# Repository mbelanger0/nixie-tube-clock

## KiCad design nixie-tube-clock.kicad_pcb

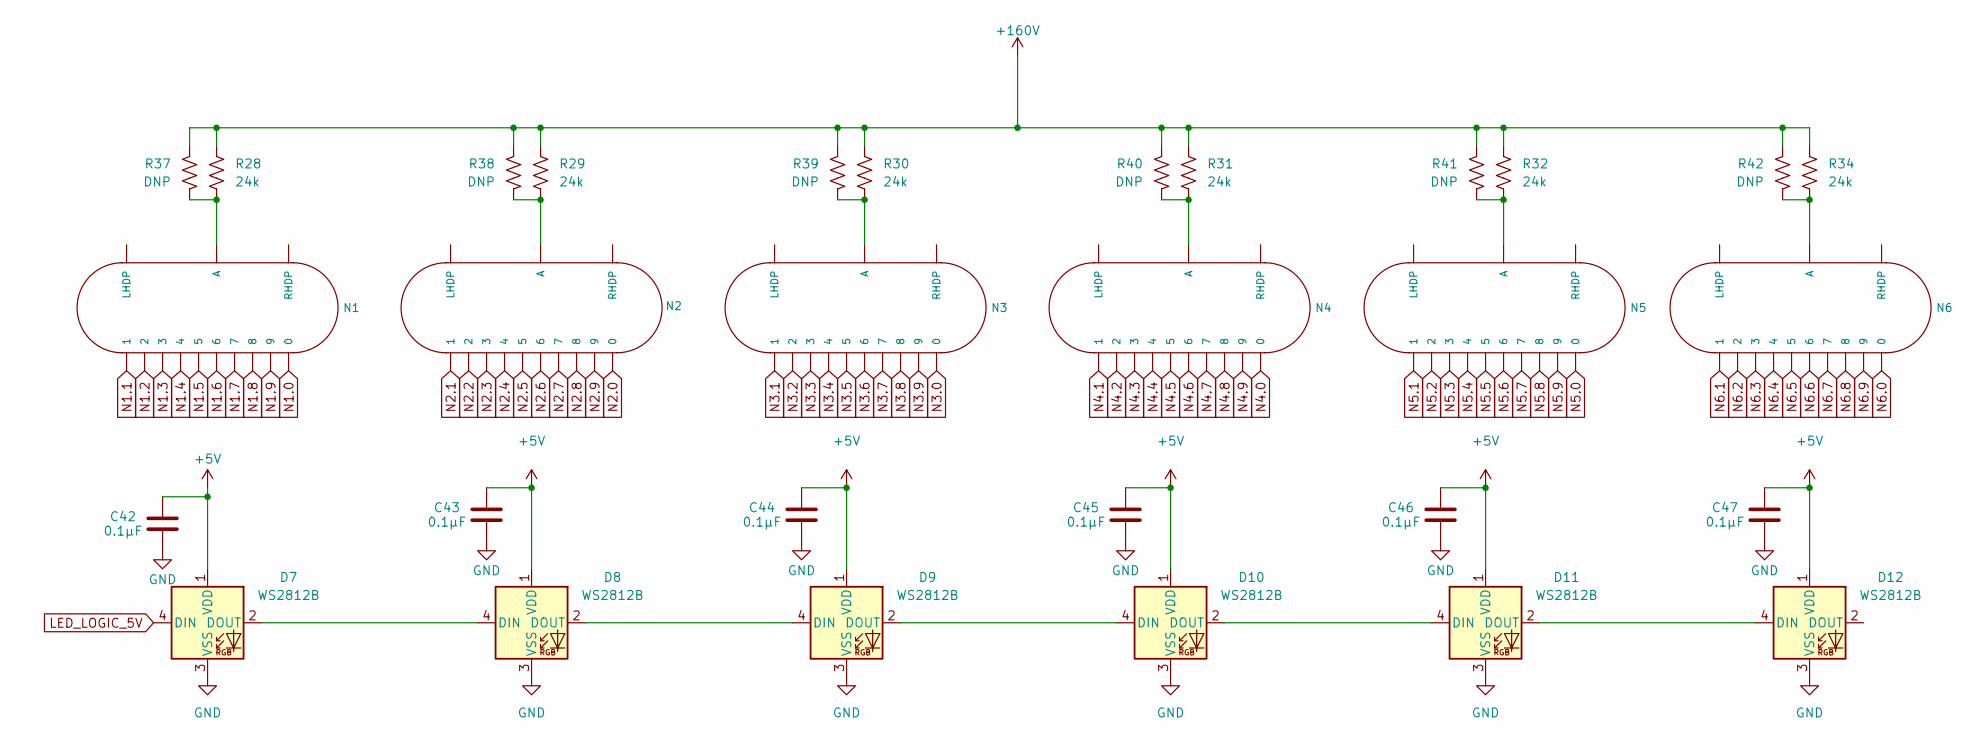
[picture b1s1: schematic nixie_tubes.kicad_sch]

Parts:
C42, C43, C44, C45, C46, C47: 0.1µF; C_0603_1608Metric; DigikeyPN 1276-1033-1-ND
D7, D8, D9, D10, D11, D12: WS2812B; LED_WS2812B_PLCC4_5.0x5.0mm_P3.2mm; DigikeyPN 1568-16347CT-ND
N1, N2, N3, N4, N5, N6: IN-14; nixies-us-IN-14
R28, R29, R30, R31, R32, R34: 24k; R_2512_6332Metric; DigikeyPN RMCF2512JT24K0CT-ND
R37, R38, R39, R40, R41, R42: DNP; R_Axial_DIN0207_L6.3mm_D2.5mm_P10.16mm_Horizontal; MPN PR01000102402JR500; DigikeyPN 56-PR01000102402JR500CT-ND

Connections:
+5V: C42.1, C43.1, C44.1, C45.1, C46.1, C47.1, D7.1 (VDD), D8.1 (VDD), D9.1 (VDD), D10.1 (VDD), D11.1 (VDD), D12.1 (VDD); also elsewhere on the board
+160V: R28.1, R29.1, R30.1, R31.1, R32.1, R34.1, R37.1, R38.1, R39.1, R40.1, R41.1, R42.1; also elsewhere on the board
LED_LOGIC_5V: D7.4 (DIN); also elsewhere on the board
N1.0: N1.0; also elsewhere on the board
N1.1: N1.1; also elsewhere on the board
N1.2: N1.2; also elsewhere on the board
N1.3: N1.3; also elsewhere on the board
N1.4: N1.4; also elsewhere on the board
N1.5: N1.5; also elsewhere on the board
N1.6: N1.6; also elsewhere on the board
N1.7: N1.7; also elsewhere on the board
N1.8: N1.8; also elsewhere on the board
N1.9: N1.9; also elsewhere on the board
N2.0: N2.0; also elsewhere on the board
N2.1: N2.1; also elsewhere on the board
N2.2: N2.2; also elsewhere on the board
N2.3: N2.3; also elsewhere on the board
N2.4: N2.4; also elsewhere on the board
N2.5: N2.5; also elsewhere on the board
N2.6: N2.6; also elsewhere on the board
N2.7: N2.7; also elsewhere on the board
N2.8: N2.8; also elsewhere on the board
N2.9: N2.9; also elsewhere on the board
N3.0: N3.0; also elsewhere on the board
N3.1: N3.1; also elsewhere on the board
N3.2: N3.2; also elsewhere on the board
N3.3: N3.3; also elsewhere on the board
N3.4: N3.4; also elsewhere on the board
N3.5: N3.5; also elsewhere on the board
N3.6: N3.6; also elsewhere on the board
N3.7: N3.7; also elsewhere on the board
N3.8: N3.8; also elsewhere on the board
N3.9: N3.9; also elsewhere on the board
N4.0: N4.0; also elsewhere on the board
N4.1: N4.1; also elsewhere on the board
N4.2: N4.2; also elsewhere on the board
N4.3: N4.3; also elsewhere on the board
N4.4: N4.4; also elsewhere on the board
N4.5: N4.5; also elsewhere on the board
N4.6: N4.6; also elsewhere on the board
N4.7: N4.7; also elsewhere on the board
N4.8: N4.8; also elsewhere on the board
N4.9: N4.9; also elsewhere on the board
N5.0: N5.0; also elsewhere on the board
N5.1: N5.1; also elsewhere on the board
N5.2: N5.2; also elsewhere on the board
N5.3: N5.3; also elsewhere on the board
N5.4: N5.4; also elsewhere on the board
N5.5: N5.5; also elsewhere on the board
N5.6: N5.6; also elsewhere on the board
N5.7: N5.7; also elsewhere on the board
N5.8: N5.8; also elsewhere on the board
N5.9: N5.9; also elsewhere on the board
N6.0: N6.0; also elsewhere on the board
N6.1: N6.1; also elsewhere on the board
N6.2: N6.2; also elsewhere on the board
N6.3: N6.3; also elsewhere on the board
N6.4: N6.4; also elsewhere on the board
N6.5: N6.5; also elsewhere on the board
N6.6: N6.6; also elsewhere on the board
N6.7: N6.7; also elsewhere on the board
N6.8: N6.8; also elsewhere on the board
N6.9: N6.9; also elsewhere on the board
unnamed: D7.2 (DOUT), D8.4 (DIN)
unnamed: D8.2 (DOUT), D9.4 (DIN)
unnamed: D9.2 (DOUT), D10.4 (DIN)
unnamed: D10.2 (DOUT), D11.4 (DIN)
unnamed: D11.2 (DOUT), D12.4 (DIN)
unnamed: N1.A, R28.2, R37.2
unnamed: N2.A, R29.2, R38.2
unnamed: N3.A, R30.2, R39.2
unnamed: N4.A, R31.2, R40.2
unnamed: N5.A, R32.2, R41.2
unnamed: N6.A, R34.2, R42.2

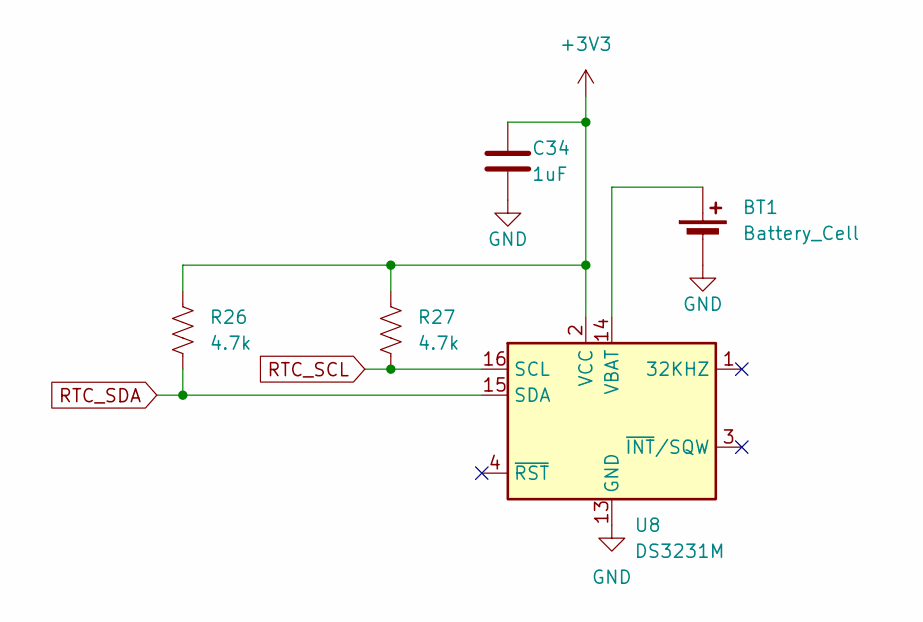
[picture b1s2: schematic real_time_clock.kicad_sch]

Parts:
BT1: Battery_Cell; BatteryHolder_Keystone_3034_1x20mm; MPN 3034; DigikeyPN 36-3034-ND
C34: 1uF; C_0603_1608Metric; DigikeyPN 1276-1184-1-ND
R26, R27: 4.7k; R_0603_1608Metric; DigikeyPN 311-4.70KHRCT-ND
U8: DS3231M; SOIC-16W_7.5x10.3mm_P1.27mm

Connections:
+3V3: C34.1, R26.1, R27.1, U8.2 (VCC); also elsewhere on the board
unnamed: BT1.1 (+), U8.14 (VBAT)
RTC_SCL: R27.2, U8.16 (SCL); also elsewhere on the board
RTC_SDA: R26.2, U8.15 (SDA); also elsewhere on the board

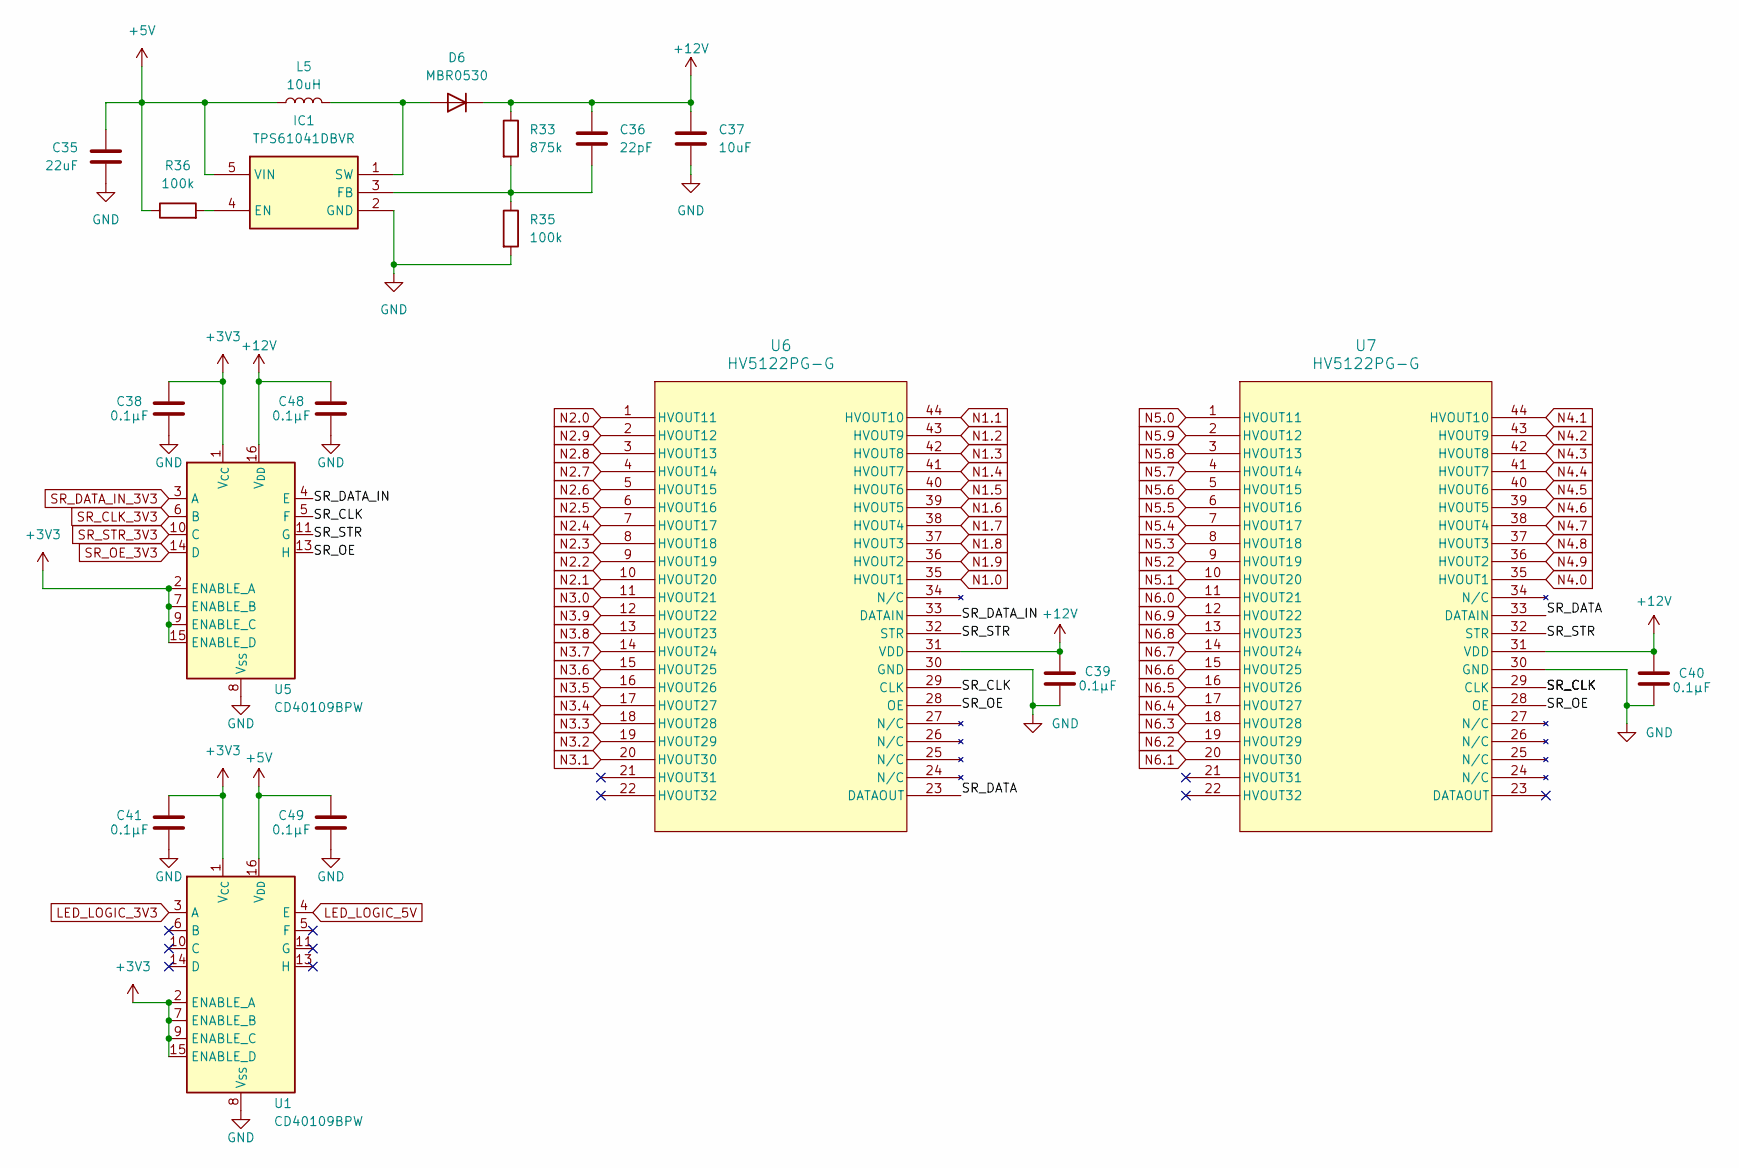
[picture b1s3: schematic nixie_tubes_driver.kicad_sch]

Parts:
C35: 22uF; C_0805_2012Metric; MPN CL21A226MQQNNNE; DigikeyPN 1276-1100-1-ND
C36: 22pF; C_0603_1608Metric; DigikeyPN 399-C0603C220J5GACTUCT-ND
C37: 10uF; C_1206_3216Metric; MPN CL31A106KAHNNNE; DigikeyPN 1276-1075-1-ND
C38, C39, C40, C41, C48, C49: 0.1µF; C_0603_1608Metric; DigikeyPN 1276-1033-1-ND
D6: MBR0530; D_SOD-123; MPN MBR0530; DigikeyPN 1655-MBR0530CT-ND
IC1: TPS61041DBVR; SOT95P280X145-5N; MPN TPS61041DBVR; DigikeyPN 296-12686-1-ND
L5: 10uH; L_1008_2520Metric; MPN 74479889310; DigikeyPN 732-74479889310CT-ND
R33: 875k; R_0805_2012Metric; DigikeyPN 2019-RN73H2ATTD8763F10CT-ND
R35, R36: 100k; R_0603_1608Metric; DigikeyPN 311-100KCRCT-ND
U1, U5: CD40109BPW; TSSOP-16_4.4x5mm_P0.65mm; DigikeyPN 296-32859-5-ND
U6, U7: HV5122PG-G; QFP44_10x10MC_MCH; MPN HV5122PG-G; LCSCPN C637042

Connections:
+3V3: C38.1, C41.1, U1.1 (V_{CC}), U1.2 (ENABLE_A), U1.7 (ENABLE_B), U1.9 (ENABLE_C), U1.15 (ENABLE_D), U5.1 (V_{CC}), U5.2 (ENABLE_A), U5.7 (ENABLE_B), U5.9 (ENABLE_C), U5.15 (ENABLE_D); also elsewhere on the board
+5V: C35.1, C49.1, IC1.5 (VIN), L5.1, R36.1, U1.16 (V_{DD}); also elsewhere on the board
+12V: C36.1, C37.1, C39.1, C40.1, C48.1, D6.1 (K), R33.1, U5.16 (V_{DD}), U6.31 (VDD), U7.31 (VDD)
/nixie_tubes_driver/SR_CLK: U5.5 (F), U6.29 (CLK), U7.29 (CLK)
/nixie_tubes_driver/SR_DATA: U6.23 (DATAOUT), U7.33 (DATAIN)
/nixie_tubes_driver/SR_DATA_IN: U5.4 (E), U6.33 (DATAIN)
/nixie_tubes_driver/SR_OE: U5.13 (H), U6.28 (OE), U7.28 (OE)
/nixie_tubes_driver/SR_STR: U5.11 (G), U6.32 (STR), U7.32 (STR)
LED_LOGIC_3V3: U1.3 (A); also elsewhere on the board
LED_LOGIC_5V: U1.4 (E); also elsewhere on the board
N1.0: U6.35 (HVOUT1); also elsewhere on the board
N1.1: U6.44 (HVOUT10); also elsewhere on the board
N1.2: U6.43 (HVOUT9); also elsewhere on the board
N1.3: U6.42 (HVOUT8); also elsewhere on the board
N1.4: U6.41 (HVOUT7); also elsewhere on the board
N1.5: U6.40 (HVOUT6); also elsewhere on the board
N1.6: U6.39 (HVOUT5); also elsewhere on the board
N1.7: U6.38 (HVOUT4); also elsewhere on the board
N1.8: U6.37 (HVOUT3); also elsewhere on the board
N1.9: U6.36 (HVOUT2); also elsewhere on the board
N2.0: U6.1 (HVOUT11); also elsewhere on the board
N2.1: U6.10 (HVOUT20); also elsewhere on the board
N2.2: U6.9 (HVOUT19); also elsewhere on the board
N2.3: U6.8 (HVOUT18); also elsewhere on the board
N2.4: U6.7 (HVOUT17); also elsewhere on the board
N2.5: U6.6 (HVOUT16); also elsewhere on the board
N2.6: U6.5 (HVOUT15); also elsewhere on the board
N2.7: U6.4 (HVOUT14); also elsewhere on the board
N2.8: U6.3 (HVOUT13); also elsewhere on the board
N2.9: U6.2 (HVOUT12); also elsewhere on the board
N3.0: U6.11 (HVOUT21); also elsewhere on the board
N3.1: U6.20 (HVOUT30); also elsewhere on the board
N3.2: U6.19 (HVOUT29); also elsewhere on the board
N3.3: U6.18 (HVOUT28); also elsewhere on the board
N3.4: U6.17 (HVOUT27); also elsewhere on the board
N3.5: U6.16 (HVOUT26); also elsewhere on the board
N3.6: U6.15 (HVOUT25); also elsewhere on the board
N3.7: U6.14 (HVOUT24); also elsewhere on the board
N3.8: U6.13 (HVOUT23); also elsewhere on the board
N3.9: U6.12 (HVOUT22); also elsewhere on the board
N4.0: U7.35 (HVOUT1); also elsewhere on the board
N4.1: U7.44 (HVOUT10); also elsewhere on the board
N4.2: U7.43 (HVOUT9); also elsewhere on the board
N4.3: U7.42 (HVOUT8); also elsewhere on the board
N4.4: U7.41 (HVOUT7); also elsewhere on the board
N4.5: U7.40 (HVOUT6); also elsewhere on the board
N4.6: U7.39 (HVOUT5); also elsewhere on the board
N4.7: U7.38 (HVOUT4); also elsewhere on the board
N4.8: U7.37 (HVOUT3); also elsewhere on the board
N4.9: U7.36 (HVOUT2); also elsewhere on the board
N5.0: U7.1 (HVOUT11); also elsewhere on the board
N5.1: U7.10 (HVOUT20); also elsewhere on the board
N5.2: U7.9 (HVOUT19); also elsewhere on the board
N5.3: U7.8 (HVOUT18); also elsewhere on the board
N5.4: U7.7 (HVOUT17); also elsewhere on the board
N5.5: U7.6 (HVOUT16); also elsewhere on the board
N5.6: U7.5 (HVOUT15); also elsewhere on the board
N5.7: U7.4 (HVOUT14); also elsewhere on the board
N5.8: U7.3 (HVOUT13); also elsewhere on the board
N5.9: U7.2 (HVOUT12); also elsewhere on the board
N6.0: U7.11 (HVOUT21); also elsewhere on the board
N6.1: U7.20 (HVOUT30); also elsewhere on the board
N6.2: U7.19 (HVOUT29); also elsewhere on the board
N6.3: U7.18 (HVOUT28); also elsewhere on the board
N6.4: U7.17 (HVOUT27); also elsewhere on the board
N6.5: U7.16 (HVOUT26); also elsewhere on the board
N6.6: U7.15 (HVOUT25); also elsewhere on the board
N6.7: U7.14 (HVOUT24); also elsewhere on the board
N6.8: U7.13 (HVOUT23); also elsewhere on the board
N6.9: U7.12 (HVOUT22); also elsewhere on the board
unnamed: D6.2 (A), IC1.1 (SW), L5.2
unnamed: IC1.4 (EN), R36.2
unnamed: C36.2, IC1.3 (FB), R33.2, R35.1
SR_CLK_3V3: U5.6 (B); also elsewhere on the board
SR_DATA_IN_3V3: U5.3 (A); also elsewhere on the board
SR_OE_3V3: U5.14 (D); also elsewhere on the board
SR_STR_3V3: U5.10 (C); also elsewhere on the board

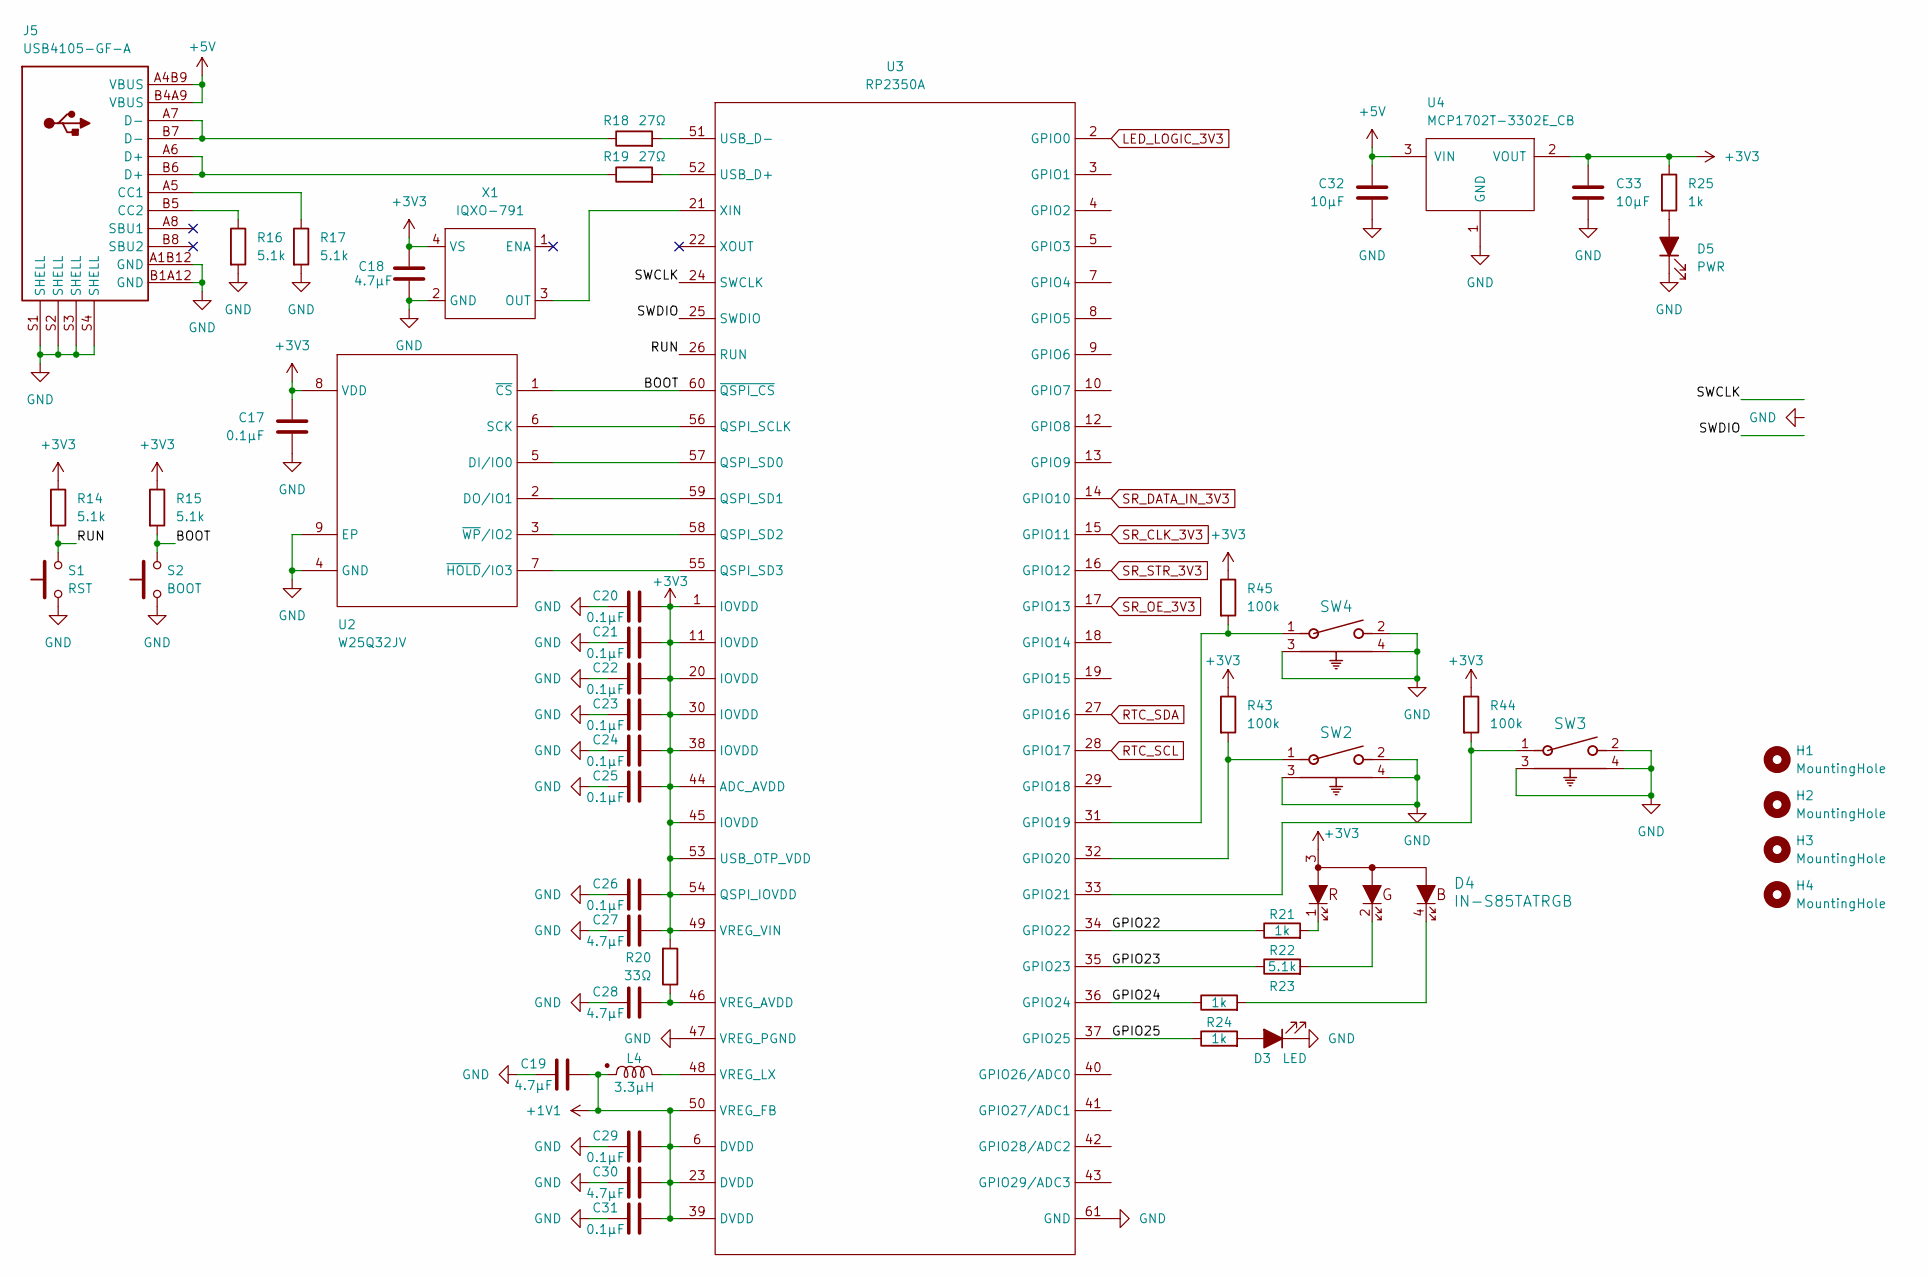
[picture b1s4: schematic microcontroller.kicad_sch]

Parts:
C17, C20, C21, C22, C23, C24, C25, C26, C29, C31: 0.1µF; C_0603_1608Metric; DigikeyPN 1276-1033-1-ND
C18, C19, C27, C28, C30: 4.7µF; C_0603_1608Metric; DigikeyPN 490-GRM188Z71C475KE21DCT-ND
C32, C33: 10µF; C_0603_1608Metric; DigikeyPN 490-18214-1-ND
D3: LED; LED_0805_2012Metric; DigikeyPN 1497-XZCM2MOK54WA-1VFCT-ND
D4: IN-S85TATRGB; DigikeyPN 1830-1086-1-ND
D5: PWR; LED_0805_2012Metric; DigikeyPN 160-1887-1-ND
H1, H2, H3, H4: MountingHole; MountingHole_3.2mm_M3
J5: USB4105-GF-A; DigikeyPN 2073-USB4105-GF-ACT-ND
L4: 3.3µH; AOTA-B201610S3R3-101-T
R14, R15, R16, R17, R22: 5.1k; R_0603_1608Metric; DigikeyPN P5.10KHCT-ND
R18, R19: 27Ω; R_0603_1608Metric; DigikeyPN 311-27.0HRCT-ND
R20: 33Ω; R_0603_1608Metric; DigikeyPN 13-RC0603FR-0733RLCT-ND
R21, R23, R24, R25: 1k; R_0603_1608Metric; DigikeyPN 311-1.00KHRCT-ND
R43, R44, R45: 100k; R_0603_1608Metric
S1: RST; SW_SPST_B3U-1000P; DigikeyPN SW1020CT-ND
S2: BOOT; SW_SPST_B3U-1000P; DigikeyPN SW1020CT-ND
SW2, SW3, SW4: 1825027-8; SW2_1825027-C_TEC; MPN 1825027-8; DigikeyPN 450-1657-ND
U2: W25Q32JV; WSON-8-1EP_6x5mm_P1.27mm_EP3.4x4.3mm; DigikeyPN W25Q32JVZPIQ TR
U3: RP2350A; RP2350A_QFN-60_EP_7.75x7.75_Pitch0.4mm; DigikeyPN 2648-SC1509-A4CT-ND
U4: MCP1702T-3302E_CB; SOT-23-3
X1: IQXO-791

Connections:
+1V1: C19.2, C29.2, C30.2, C31.2, L4.1, U3.6 (DVDD), U3.23 (DVDD), U3.39 (DVDD), U3.50 (VREG_FB)
+3V3: C17.2, C18.2, C20.2, C21.2, C22.2, C23.2, C24.2, C25.2, C26.2, C27.2, C33.1, D4.3, R14.1, R15.1, R20.2, R25.1, R43.1, R44.1, R45.1, U2.8 (VDD), U3.1 (IOVDD), U3.11 (IOVDD), U3.20 (IOVDD), U3.30 (IOVDD), U3.38 (IOVDD), U3.44 (ADC_AVDD), U3.45 (IOVDD), U3.49 (VREG_VIN), U3.53 (USB_OTP_VDD), U3.54 (QSPI_IOVDD), U4.2 (VOUT), X1.4 (VS); also elsewhere on the board
+5V: C32.2, J5.A4B9 (VBUS), J5.B4A9 (VBUS), U4.3 (VIN); also elsewhere on the board
/microcontroller/BOOT: R15.2, S2.2, U2.1 (~CS), U3.60 (~QSPI_CS); also elsewhere on the board
/microcontroller/GPIO22: R21.1, U3.34 (GPIO22)
/microcontroller/GPIO23: R22.1, U3.35 (GPIO23)
/microcontroller/GPIO24: R23.1, U3.36 (GPIO24)
/microcontroller/GPIO25: R24.1, U3.37 (GPIO25)
/microcontroller/RUN: R14.2, S1.2, U3.26 (RUN); also elsewhere on the board
/microcontroller/SWCLK: U3.24 (SWCLK)
/microcontroller/SWDIO: U3.25 (SWDIO)
LED_LOGIC_3V3: U3.2 (GPIO0); also elsewhere on the board
unnamed: D3.2 (A), R24.2
unnamed: D4.1, R21.2
unnamed: D4.2, R22.2
unnamed: D4.4, R23.2
unnamed: D5.2 (A), R25.2
unnamed: J5.A5 (CC1), R17.1
unnamed: J5.B5 (CC2), R16.1
unnamed: J5.A6 (D+), J5.B6 (D+), R19.1
unnamed: J5.A7 (D-), J5.B7 (D-), R18.1
unnamed: U2.5 (DI/IO0), U3.57 (QSPI_SD0)
unnamed: U2.2 (DO/IO1), U3.59 (QSPI_SD1)
unnamed: U2.6 (SCK), U3.56 (QSPI_SCLK)
unnamed: U2.7 (~HOLD/IO3), U3.55 (QSPI_SD3)
unnamed: U2.3 (~WP/IO2), U3.58 (QSPI_SD2)
unnamed 121: R45.2, SW4.1, U3.31 (GPIO19); also elsewhere on the board
unnamed 122: R43.2, SW2.1, U3.32 (GPIO20); also elsewhere on the board
unnamed 123: R44.2, SW3.1, U3.33 (GPIO21); also elsewhere on the board
unnamed: R19.2, U3.52 (USB_D+)
unnamed: R18.2, U3.51 (USB_D-)
unnamed: C28.2, R20.1, U3.46 (VREG_AVDD)
unnamed: L4.2, U3.48 (VREG_LX)
unnamed: U3.21 (XIN), X1.3 (OUT)
RTC_SCL: U3.28 (GPIO17); also elsewhere on the board
RTC_SDA: U3.27 (GPIO16); also elsewhere on the board
SR_CLK_3V3: U3.15 (GPIO11); also elsewhere on the board
SR_DATA_IN_3V3: U3.14 (GPIO10); also elsewhere on the board
SR_OE_3V3: U3.17 (GPIO13); also elsewhere on the board
SR_STR_3V3: U3.16 (GPIO12); also elsewhere on the board

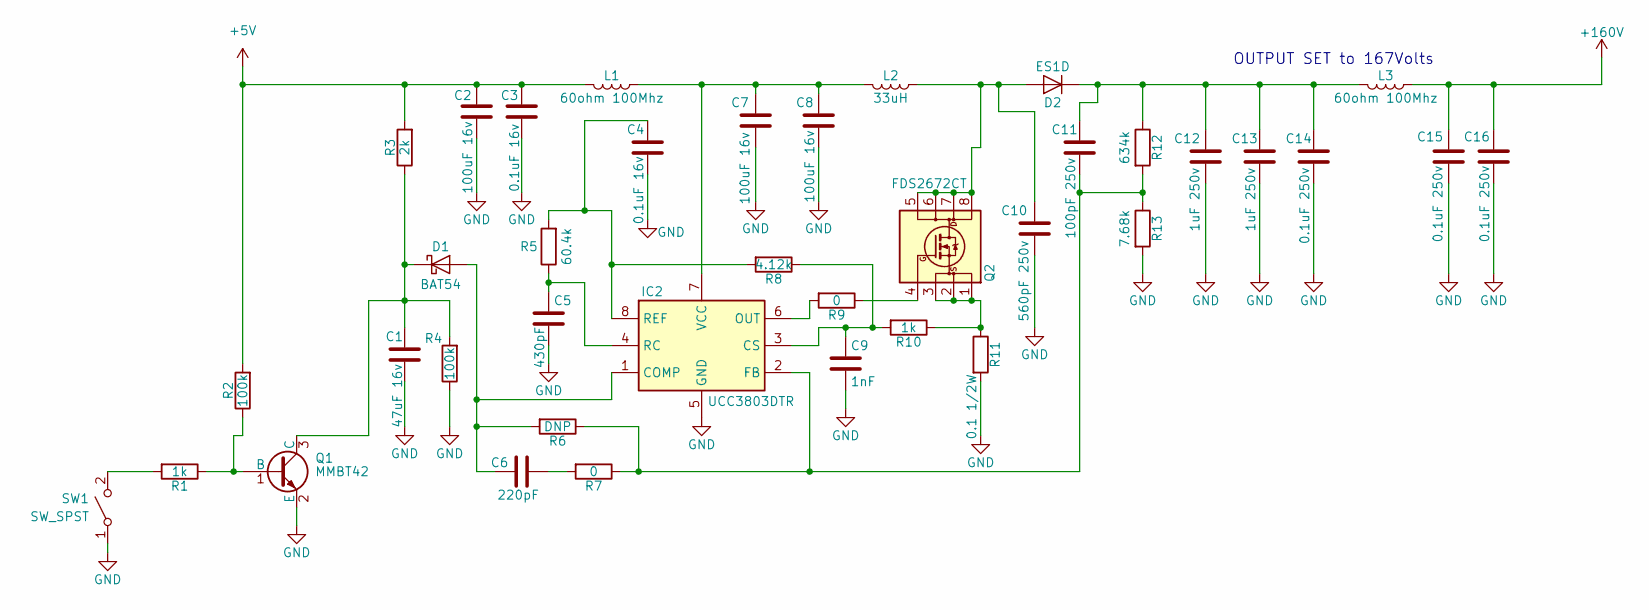
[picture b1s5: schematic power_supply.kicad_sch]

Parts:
C1: 47uF 16v; C_1206_3216Metric_Pad1.33x1.80mm_HandSolder; MPN C3216X5R1C476M160AB; DigikeyPN 445-6003-1-ND
C2, C7, C8: 100uF 16v; C_1210_3225Metric_Pad1.33x2.70mm_HandSolder; MPN EMK325ABJ107MM-P; DigikeyPN 587-5426-1-ND
C3, C4: 0.1uF 16v; C_0603_1608Metric; MPN C0603C104K4RACTU; DigikeyPN 399-C0603C104K4RACTUCT-ND
C5: 430pF; C_0805_2012Metric_Pad1.18x1.45mm_HandSolder; MPN CC0805JRNPO9BN431; DigikeyPN 311-4238-1-ND
C6: 220pF; C_0805_2012Metric_Pad1.18x1.45mm_HandSolder; MPN 885012207029; DigikeyPN 732-8029-1-ND
C9: 1nF; C_0805_2012Metric_Pad1.18x1.45mm_HandSolder; MPN C0805C102J5GACTU; DigikeyPN 399-C0805C102J5GACTUCT-ND
C10: 560pF 250v; C_0603_1608Metric_Pad1.08x0.95mm_HandSolder; MPN C0603C561JAGAC7867; DigikeyPN 399-C0603C561JAGACTUCT-ND
C11: 100pF 250v; C_0805_2012Metric_Pad1.18x1.45mm_HandSolder; MPN GRM21A5C2E101JW01D; DigikeyPN 490-5542-1-ND
C12, C13: 1uF 250v; C_2220_5750Metric_Pad1.97x5.40mm_HandSolder; MPN GRM55DR72E105KW01L; DigikeyPN 490-3550-1-ND
C14, C15, C16: 0.1uF 250v; C_0805_2012Metric_Pad1.18x1.45mm_HandSolder; MPN CGA4J3X7T2E104M125AE; DigikeyPN 445-7965-1-ND
D1: BAT54; D_SOD-323_HandSoldering; MPN BAT54HT1G; DigikeyPN BAT54HT1GOSCT-ND
D2: ES1D; D_SMA_Handsoldering; MPN ES1D; DigikeyPN ES1DFSCT-ND
IC2: UCC3803DTR; SOIC127P600X175-8N; MPN UCC3803DTR; DigikeyPN 296-38327-1-ND
L1: 60ohm 100Mhz; L_0805_2012Metric; MPN MH2029-600Y; DigikeyPN MH2029-600YCT-ND
L2: 33uH; WE-PD_1210; MPN 7447709330; DigikeyPN 732-1244-1-ND
L3: 60ohm 100Mhz; L_0805_2012Metric; MPN MH2029-600Y; DigiKeyPN MH2029-600YCT-ND
Q1: MMBT42; SOT-23; MPN MMBTA42-TP; DigikeyPN MMBTA42TPMSCT-ND
Q2: FDS2672CT; SOIC-8_3.9x4.9mm_P1.27mm; MPN FDS2672CT-ND
R1: 1k; R_0603_1608Metric; MPN RC0603FR-071KL; DigikeyPN 311-1.00KHRCT-ND
R2, R4: 100k; R_0805_2012Metric_Pad1.20x1.40mm_HandSolder; MPN CRCW0805100KFKEA; DigikeyPN 541-100KCCT-ND
R3: 2k; R_0805_2012Metric_Pad1.20x1.40mm_HandSolder; MPN CRCW08052K00FKEA; DigikeyPN 541-2.00KCCT-ND
R5: 60.4k; R_0805_2012Metric_Pad1.20x1.40mm_HandSolder; MPN CRCW080560K4FKEA; DigikeyPN 541-60.4KCCT-ND
R6: DNP; R_0805_2012Metric_Pad1.20x1.40mm_HandSolder
R7, R9: 0; R_0603_1608Metric; MPN RC0603JR-070RL; DigikeyPN 311-0.0GRCT-ND
R8: 4.12k; R_0805_2012Metric_Pad1.20x1.40mm_HandSolder; MPN CRCW08054K12FKEA; DigikeyPN 541-4.12KCCT-ND
R10: 1k; R_0805_2012Metric_Pad1.20x1.40mm_HandSolder; MPN ERJ-P06J102V; DigikeyPN P1.0KADCT-ND
R11: 0.1 1/2W; R_0805_2012Metric_Pad1.20x1.40mm_HandSolder; MPN ERJ-6DSFR10V; DigikeyPN P19308CT-ND
R12: 634k; R_0805_2012Metric_Pad1.20x1.40mm_HandSolder; MPN CRCW0805634KFKEA; DigikeyPN 541-634KCCT-ND
R13: 7.68k; R_0805_2012Metric_Pad1.20x1.40mm_HandSolder; MPN RC1206FR-077K68L; DigikeyPN 311-7.68KFRCT-ND
SW1: SW_SPST; PinHeader_1x02_P2.54mm_Vertical

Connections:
+5V: C2.1, C3.1, L1.2, R2.2, R3.2; also elsewhere on the board
+160V: C15.1, C16.1, L3.1; also elsewhere on the board
unnamed: C1.1, D1.1 (K), Q1.3 (C), R3.1, R4.2
unnamed: C10.1, D2.2 (A), L2.1, Q2.5 (D), Q2.6 (D), Q2.7 (D), Q2.8 (D)
unnamed: C11.1, C12.1, C13.1, C14.1, D2.1 (K), L3.2, R12.1
unnamed: C9.1, IC2.3 (CS), R8.1, R10.2
unnamed: C11.2, IC2.2 (FB), R6.1, R7.1, R12.2, R13.1
unnamed: IC2.6 (OUT), R9.2
unnamed: C5.1, IC2.4 (RC), R5.1
unnamed: C7.1, C8.1, IC2.7 (VCC), L1.1, L2.2
unnamed: Q1.1 (B), R1.1, R2.1
unnamed: Q2.4 (G), R9.1
unnamed: Q2.1 (S), Q2.2 (S), Q2.3 (S), R10.1, R11.1
unnamed: R1.2, SW1.2 (B)

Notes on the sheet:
OUTPUT SET to 167Volts

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
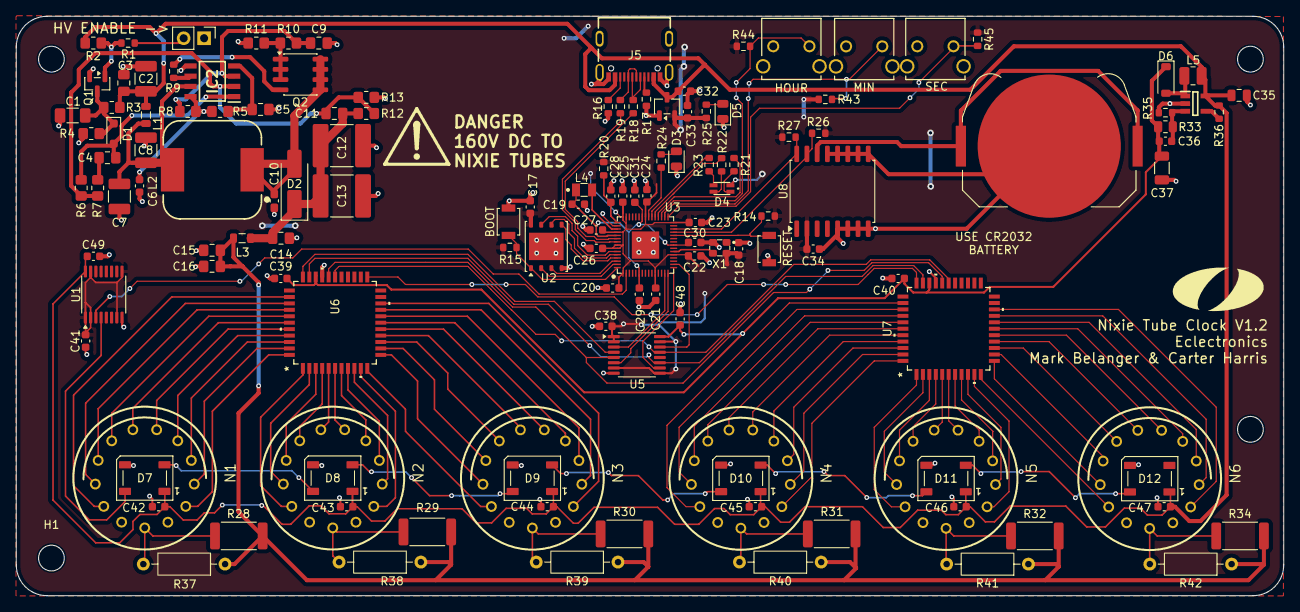
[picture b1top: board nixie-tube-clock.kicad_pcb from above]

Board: 2 copper layers, 157.5 x 72.0 mm, 144 parts (0 on the bottom side), 137 nets.

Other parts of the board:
BOOT: BOOT; SW_SPST_B3U-1000P
HOUR: 1825027-8; SW2_1825027-C_TEC
MIN: 1825027-8; SW2_1825027-C_TEC
OlinLogoLg: G***; OlinLogoLg
RESET: RST; SW_SPST_B3U-1000P
SEC: 1825027-8; SW2_1825027-C_TEC
svg2mod: G***; OlinLogoHuge

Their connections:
/microcontroller/BOOT: BOOT.2; also elsewhere on the board
/microcontroller/RUN: RESET.2; also elsewhere on the board
unnamed 121: SEC.1; also elsewhere on the board
unnamed 122: MIN.1; also elsewhere on the board
unnamed 123: HOUR.1; also elsewhere on the board

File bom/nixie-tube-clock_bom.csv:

Reference,Qty,Value,Footprint,MFN,MPN,DigikeyPN,Stocked
BT1,1,Battery_Cell,Battery:BatteryHolder_Keystone_3034_1x20mm,Keystone Electronics,3034,36-3034-ND,
C1,1,47uF 16v,Capacitor_SMD:C_1206_3216Metric_Pad1.33x1.80mm_HandSolder,TDK,C3216X5R1C476M160AB,445-6003-1-ND,
"C2,C7,C8",3,100uF 16v,Capacitor_SMD:C_1210_3225Metric_Pad1.33x2.70mm_HandSolder,Taiyo Yuden,EMK325ABJ107MM-P,587-5426-1-ND,
"C3,C4",2,0.1uF 16v,Capacitor_SMD:C_0603_1608Metric,KEMET,C0603C104K4RACTU,399-C0603C104K4RACTUCT-ND,
C5,1,430pF,Capacitor_SMD:C_0805_2012Metric_Pad1.18x1.45mm_HandSolder,YAGEO,CC0805JRNPO9BN431,311-4238-1-ND,
C6,1,220pF,Capacitor_SMD:C_0805_2012Metric_Pad1.18x1.45mm_HandSolder,Würth Elektronik,885012207029,732-8029-1-ND,
C9,1,1nF,Capacitor_SMD:C_0805_2012Metric_Pad1.18x1.45mm_HandSolder,KEMET,C0805C102J5GACTU,399-C0805C102J5GACTUCT-ND,
C10,1,560pF 250v,Capacitor_SMD:C_0603_1608Metric_Pad1.08x0.95mm_HandSolder,KEMET,C0603C561JAGAC7867,399-C0603C561JAGACTUCT-ND,
C11,1,100pF 250v,Capacitor_SMD:C_0805_2012Metric_Pad1.18x1.45mm_HandSolder,Murata Electronics,GRM21A5C2E101JW01D,490-5542-1-ND,
"C12,C13",2,1uF 250v,Capacitor_SMD:C_2220_5750Metric_Pad1.97x5.40mm_HandSolder,Murata Electronics,GRM55DR72E105KW01L,490-3550-1-ND,
"C14,C15,C16",3,0.1uF 250v,Capacitor_SMD:C_0805_2012Metric_Pad1.18x1.45mm_HandSolder,TDK,CGA4J3X7T2E104M125AE,445-7965-1-ND,
"C17,C20,C21,C22,C23,C24,C25,C26,C29,C31,C38,C39,C40,C41,C42,C43,C44,C45,C46,C47,C48,C49",22,0.1µF,Capacitor_SMD:C_0603_1608Metric,Samsung Electro-Mechanics,CL10B104JB8NNNC,1276-1033-1-ND,
"C18,C19,C27,C28,C30",5,4.7µF,Capacitor_SMD:C_0603_1608Metric,Murata Electronics,GRM188Z71C475KE21D,490-GRM188Z71C475KE21DCT-ND,
"C32,C33",2,10µF,Capacitor_SMD:C_0603_1608Metric,Murata Electronics,GRM188R61E106KA73D,490-18214-1-ND,
C34,1,1uF,Capacitor_SMD:C_0603_1608Metric,Samsung Electro-Mechanics,CL10B105KA8NNNC,1276-1184-1-ND,
C35,1,22uF,Capacitor_SMD:C_0805_2012Metric,Samsung Electro-Mechanics,CL21A226MQQNNNE,1276-1100-1-ND,
C36,1,22pF,Capacitor_SMD:C_0603_1608Metric,KEMET,C0603C220J5GACTU,399-C0603C220J5GACTUCT-ND,
C37,1,10uF,Capacitor_SMD:C_1206_3216Metric,Samsung Electro-Mechanics,CL31A106KAHNNNE,1276-1075-1-ND,
D1,1,BAT54,Diode_SMD:D_SOD-323_HandSoldering,onsemi,BAT54HT1G,BAT54HT1GOSCT-ND,
D2,1,ES1D,Diode_SMD:D_SMA_Handsoldering,onsemi,ES1D,ES1DFSCT-ND,
D3,1,LED,LED_SMD:LED_0805_2012Metric,SunLED,XZCM2MOK54WA-1VF,1497-XZCM2MOK54WA-1VFCT-ND,
D4,1,IN-S85TATRGB,Eclectronics:IN-S85TATRGB,Inolux,IN-S85TATRGB,1830-1086-1-ND,Y
D5,1,PWR,LED_SMD:LED_0805_2012Metric,Lite-On Inc.,LTST-C170TGKT,160-1887-1-ND,
D6,1,MBR0530,Diode_SMD:D_SOD-123,SMC Diode Solutions,MBR0530,1655-MBR0530CT-ND,
"D7,D8,D9,D10,D11,D12",6,WS2812B,LED_SMD:LED_WS2812B_PLCC4_5.0x5.0mm_P3.2mm,SparkFun Electronics,16347,1568-16347CT-ND,
"H1,H2,H3,H4",4,MountingHole,MountingHole:MountingHole_3.2mm_M3,,,,Y
IC1,1,TPS61041DBVR,eclectronics_nixie_footprints:SOT95P280X145-5N,Texas Instruments,TPS61041DBVR,296-12686-1-ND,
IC2,1,UCC3803DTR,eclectronics_nixie_footprints:SOIC127P600X175-8N,Texas Instruments,UCC3803DTR,296-38327-1-ND,
J5,1,USB4105-GF-A,Eclectronics:USB4105-GF-A,GCT,USB4105-GF-A,2073-USB4105-GF-ACT-ND,Y
"L1,L3",2,60ohm 100Mhz,Inductor_SMD:L_0805_2012Metric,Bourns Inc.,MH2029-600Y,MH2029-600YCT-ND,
L2,1,33uH,eclectronics_nixie_footprints:WE-PD_1210,Würth Elektronik,7447709330,732-1244-1-ND,
L4,1,3.3µH,Eclectronics:AOTA-B201610S3R3-101-T,Abracon LLC,AOTA-B201610S3R3-101-T,535-AOTA-B201610S3R3-101-TCT-ND,Y
L5,1,10uH,Inductor_SMD:L_1008_2520Metric,Würth Elektronik,74479889310,732-74479889310CT-ND,
"N1,N2,N3,N4,N5,N6",6,IN-14,eclectronics_nixie_footprints:nixies-us-IN-14,,,,Y
Q1,1,MMBT42,Package_TO_SOT_SMD:SOT-23,MCC (Micro Commercial Components),MMBTA42-TP,MMBTA42TPMSCT-ND,
Q2,1,FDS2672CT,Package_SO:SOIC-8_3.9x4.9mm_P1.27mm,onsemi,FDS2672CT-ND,FDS2672CT-ND,
"R1,R21,R23,R24,R25",5,1k,Resistor_SMD:R_0603_1608Metric,YAGEO,RC0603FR-071KL,311-1.00KHRCT-ND,
"R2,R4",2,100k,Resistor_SMD:R_0805_2012Metric_Pad1.20x1.40mm_HandSolder,Vishay Dale,CRCW0805100KFKEA,541-100KCCT-ND,
R3,1,2k,Resistor_SMD:R_0805_2012Metric_Pad1.20x1.40mm_HandSolder,Vishay Dale,CRCW08052K00FKEA,541-2.00KCCT-ND,
R5,1,60.4k,Resistor_SMD:R_0805_2012Metric_Pad1.20x1.40mm_HandSolder,Vishay Dale,CRCW080560K4FKEA,541-60.4KCCT-ND,
R6,1,DNP,Resistor_SMD:R_0805_2012Metric_Pad1.20x1.40mm_HandSolder,,,,Y
"R7,R9",2,0,Resistor_SMD:R_0603_1608Metric,YAGEO,RC0603JR-070RL,311-0.0GRCT-ND,
R8,1,4.12k,Resistor_SMD:R_0805_2012Metric_Pad1.20x1.40mm_HandSolder,Vishay Dale,CRCW08054K12FKEA,541-4.12KCCT-ND,
R10,1,1k,Resistor_SMD:R_0805_2012Metric_Pad1.20x1.40mm_HandSolder,Panasonic Electronic Components,ERJ-P06J102V,P1.0KADCT-ND,
R11,1,0.1 1/2W,Resistor_SMD:R_0805_2012Metric_Pad1.20x1.40mm_HandSolder,Panasonic Electronic Components,ERJ-6DSFR10V,P19308CT-ND,
R12,1,634k,Resistor_SMD:R_0805_2012Metric_Pad1.20x1.40mm_HandSolder,Vishay Dale,CRCW0805634KFKEA,541-634KCCT-ND,
R13,1,7.68k,Resistor_SMD:R_0805_2012Metric_Pad1.20x1.40mm_HandSolder,YAGEO,RC1206FR-077K68L,311-7.68KFRCT-ND,
"R14,R15,R16,R17,R22",5,5.1k,Resistor_SMD:R_0603_1608Metric,Panasonic Industry,ERJ-3EKF5101V,P5.10KHCT-ND,
"R18,R19",2,27Ω,Resistor_SMD:R_0603_1608Metric,YAGEO,RC0603FR-0727RL,311-27.0HRCT-ND,
R20,1,33Ω,Resistor_SMD:R_0603_1608Metric,YAGEO,RC0603FR-0733RL,13-RC0603FR-0733RLCT-ND,
"R26,R27",2,4.7k,Resistor_SMD:R_0603_1608Metric,YAGEO,RC0603FR-074K7L,311-4.70KHRCT-ND,
"R28,R29,R30,R31,R32,R34",6,24k,Resistor_SMD:R_2512_6332Metric,Stackpole Electronics Inc,RMCF2512JT24K0,RMCF2512JT24K0CT-ND,
R33,1,875k,Resistor_SMD:R_0805_2012Metric,"KOA Speer Electronics, Inc.",RN73H2ATTD8763F10,2019-RN73H2ATTD8763F10CT-ND,
"R35,R36,R43,R44,R45",5,100k,Resistor_SMD:R_0603_1608Metric,YAGEO,RC0805FR-07100KL,311-100KCRCT-ND,
"R37,R38,R39,R40,R41,R42",6,DNP,Resistor_THT:R_Axial_DIN0207_L6.3mm_D2.5mm_P10.16mm_Horizontal,Vishay Beyschlag/Draloric/BC Components,PR01000102402JR500,56-PR01000102402JR500CT-ND,
S1,1,RST,Button_Switch_SMD:SW_SPST_B3U-1000P,Omron Electronics Inc-EMC Div,B3U-1000P,SW1020CT-ND,Y
S2,1,BOOT,Button_Switch_SMD:SW_SPST_B3U-1000P,Omron Electronics Inc-EMC Div,B3U-1000P,SW1020CT-ND,Y
SW1,1,SW_SPST,Connector_PinHeader_2.54mm:PinHeader_1x02_P2.54mm_Vertical,,,,Y
"SW2,SW3,SW4",3,1825027-8,carter_kicad_footprints:SW2_1825027-C_TEC,TE Connectivity ALCOSWITCH Switches,1825027-8,450-1657-ND,
"U1,U5",2,CD40109BPW,Package_SO:TSSOP-16_4.4x5mm_P0.65mm,Texas Instruments,CD40109BPW,296-32859-5-ND,
U2,1,W25Q32JV,Package_SON:WSON-8-1EP_6x5mm_P1.27mm_EP3.4x4.3mm,Winbond Electronics,W25Q32JVZPIQ TR,256-W25Q32JVZPIQTRCT-ND,
U3,1,RP2350A,Eclectronics:RP2350A_QFN-60_EP_7.75x7.75_Pitch0.4mm,Raspberry Pi,SC1509-A4,2648-SC1509-A4CT-ND,
U4,1,MCP1702T-3302E_CB,Package_TO_SOT_SMD:SOT-23-3,Microchip Technology,MCP1702T-3302E/CB,MCP1702T-3302E/CBCT-ND,
"U6,U7",2,HV5122PG-G,eclectronics_nixie_footprints:QFP44_10x10MC_MCH,Microchip Technology,HV5122PG-G,HV5122PG-G-ND,
U8,1,DS3231M,Package_SO:SOIC-16W_7.5x10.3mm_P1.27mm,Analog Devices Inc./Maxim Integrated,DS3231M+TRL,DS3231M+TRLCT-ND,
X1,1,IQXO-791,Eclectronics:IQXO-791,,,,Y

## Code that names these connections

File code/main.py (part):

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Nixie Tube Clock - CircuitPython firmware for RP2350

Hardware (from schematic):
  RTC:  DS3231M on I2C0, GPIO16=SDA, GPIO17=SCL (3.3V pull-ups on board)
  Shift register chain: two HV5122 (U6 -> U7) driven via CD40109 level shifters
    GPIO10 -> SR_DATA_IN
    GPIO11 -> SR_CLK
    GPIO12 -> SR_STR   (strobe / latch)
    GPIO13 -> SR_OE    (output enable; HV5122 OE is ACTIVE HIGH)
  Six nixie tubes N1..N6:
    N1..N3 driven by U6 outputs HVOUT1..HVOUT30
    N4..N6 driven by U7 outputs HVOUT1..HVOUT30
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  STR is held HIGH at all times. To avoid glitching during a shift, OE
  is driven LOW while clocking in new data, then set HIGH to display.

Note on SPI: the RP2350's hardware SPI1 uses GPIO10 for SCK and GPIO11 for
TX, but the board wires them the other way (GPIO10=data, GPIO11=clock), so
this script bit-bangs the shift register. 64 bits once per second is trivial.
"""

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# ---------------------------------------------------------------------------
# Pin assignments
# ---------------------------------------------------------------------------
PIN_SR_DATA = board.GP10
PIN_SR_CLK = board.GP11
PIN_SR_STR = board.GP12
PIN_SR_OE = board.GP13

PIN_I2C_SDA = board.GP16
PIN_I2C_SCL = board.GP17
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
    print()
    print("[INIT] Setting up shift register outputs")
    nix = NixieDriver(PIN_SR_DATA, PIN_SR_CLK, PIN_SR_STR, PIN_SR_OE)

    print()
    print("[LOOP] Entering main loop (50 ms poll interval)")
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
